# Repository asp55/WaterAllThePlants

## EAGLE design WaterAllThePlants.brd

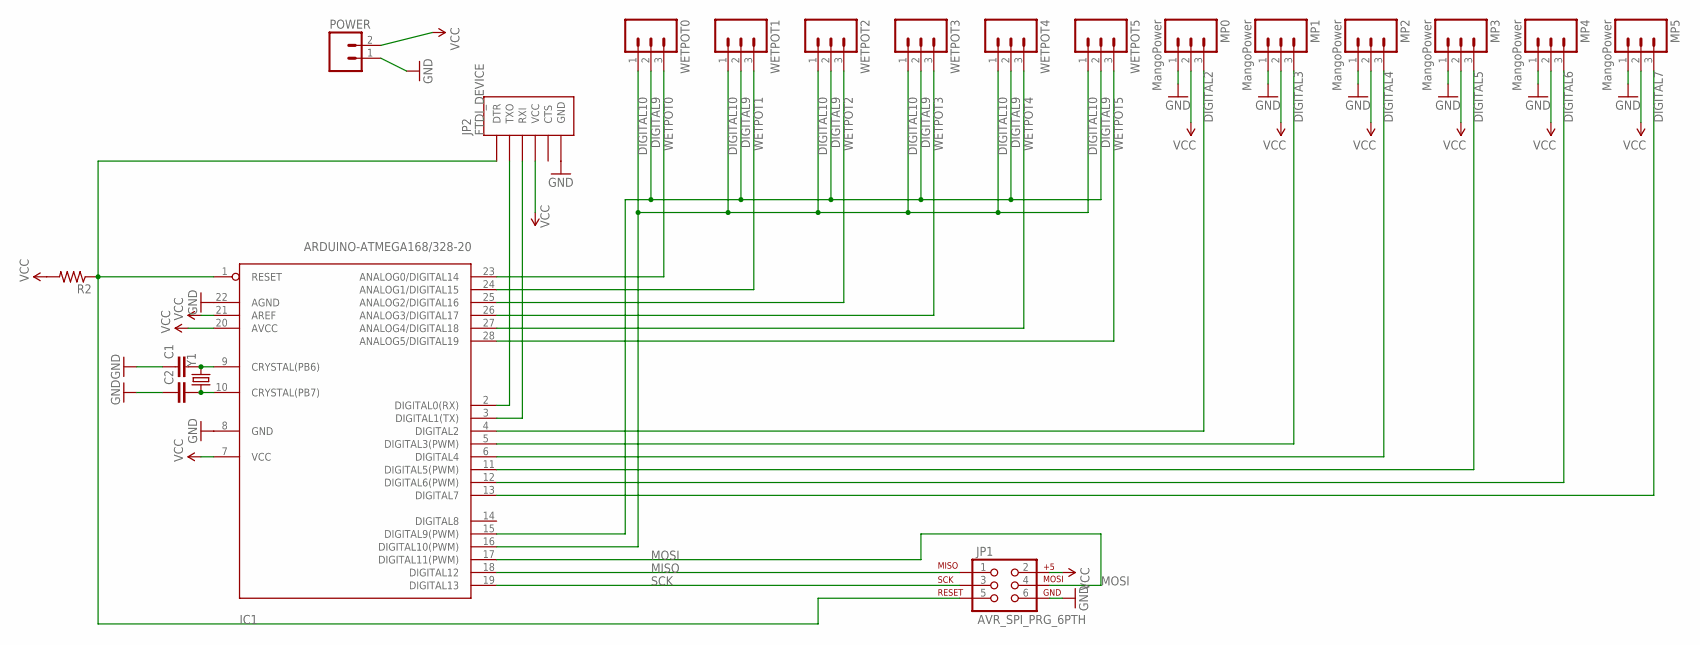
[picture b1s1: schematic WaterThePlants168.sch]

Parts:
C1, C2: CAPPTH2; CAP-PTH-SMALL2
IC1: ARDUINO-ATMEGA168/328-20; DIL28-3
JP1: AVR_SPI_PRG_6PTH; 2X3
JP2: FTDI_DEVICE; FTDI_DEVICE_SIDE
MP0, MP1, MP2, MP3, MP4, MP5: MangoPower; 1X03
POWER: M02POLAR; MOLEX-1X2
R2: RESISTORAXIAL-0.3; AXIAL-0.3
WETPOT0, WETPOT1, WETPOT2, WETPOT3, WETPOT4, WETPOT5: M03PTH; 1X03
Y1: CRYSTALHC49US; HC49US

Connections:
DIGITAL2: IC1.4 (DIGITAL2), MP0.3
DIGITAL3: IC1.5 (DIGITAL3(PWM)), MP1.3
DIGITAL4: IC1.6 (DIGITAL4), MP2.3
DIGITAL5: IC1.11 (DIGITAL5(PWM)), MP3.3
DIGITAL6: IC1.12 (DIGITAL6(PWM)), MP4.3
DIGITAL7: IC1.13 (DIGITAL7), MP5.3
DIGITAL9: IC1.15 (DIGITAL9(PWM)), WETPOT0.2, WETPOT1.2, WETPOT2.2, WETPOT3.2, WETPOT4.2, WETPOT5.2
DIGITAL10: IC1.16 (DIGITAL10(PWM)), WETPOT0.1, WETPOT1.1, WETPOT2.1, WETPOT3.1, WETPOT4.1, WETPOT5.1
GND: C1.1, C2.1, IC1.8 (GND), IC1.22 (AGND), JP1.6, JP2.P$6 (GND), MP0.1, MP1.1, MP2.1, MP3.1, MP4.1, MP5.1, POWER.1
MISO: IC1.18 (DIGITAL12), JP1.1
MOSI: IC1.17 (DIGITAL11(PWM)), JP1.4
unnamed: IC1.2 (DIGITAL0(RX)), JP2.P$2 (TXO)
unnamed: IC1.3 (DIGITAL1(TX)), JP2.P$3 (RXI)
unnamed: C1.2, IC1.9 (CRYSTAL(PB6)), Y1.2
unnamed: C2.2, IC1.10 (CRYSTAL(PB7)), Y1.1
RESET: IC1.1 (RESET), JP1.5, JP2.P$1 (DTR), R2.P$1 (1)
SCK: IC1.19 (DIGITAL13), JP1.3
VCC: IC1.7 (VCC), IC1.20 (AVCC), IC1.21 (AREF), JP1.2, JP2.P$4 (VCC), MP0.2, MP1.2, MP2.2, MP3.2, MP4.2, MP5.2, POWER.2, R2.P$2 (2)
WETPOT0: IC1.23 (ANALOG0/DIGITAL14), WETPOT0.3
WETPOT1: IC1.24 (ANALOG1/DIGITAL15), WETPOT1.3
WETPOT2: IC1.25 (ANALOG2/DIGITAL16), WETPOT2.3
WETPOT3: IC1.26 (ANALOG3/DIGITAL17), WETPOT3.3
WETPOT4: IC1.27 (ANALOG4/DIGITAL18), WETPOT4.3
WETPOT5: IC1.28 (ANALOG5/DIGITAL19), WETPOT5.3

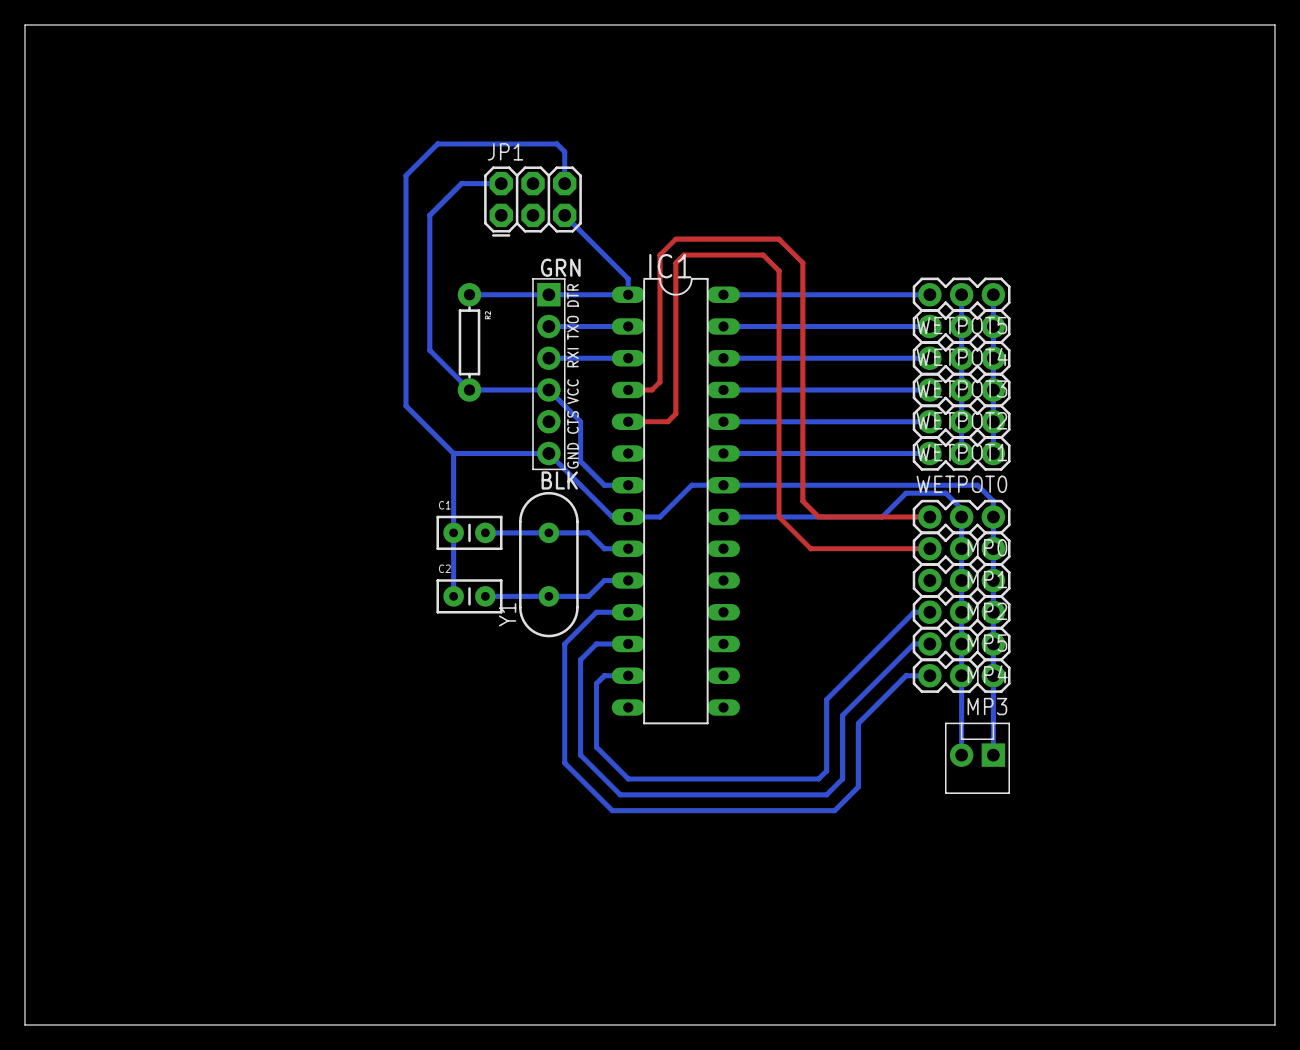
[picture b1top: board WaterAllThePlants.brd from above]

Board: 2 copper layers, 100.0 x 80.0 mm, 20 parts (0 on the bottom side), 24 nets.

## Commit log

2015-04-16 Created initial schematic and board design.
2015-04-16 Renamed board and schematic file to match project name

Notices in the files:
parts and their libraries:
SparkFun-Connectors: Licensing: Creative Commons ShareAlike 4.0 International - https://creativecommons.org/licenses/by-sa/4.0
